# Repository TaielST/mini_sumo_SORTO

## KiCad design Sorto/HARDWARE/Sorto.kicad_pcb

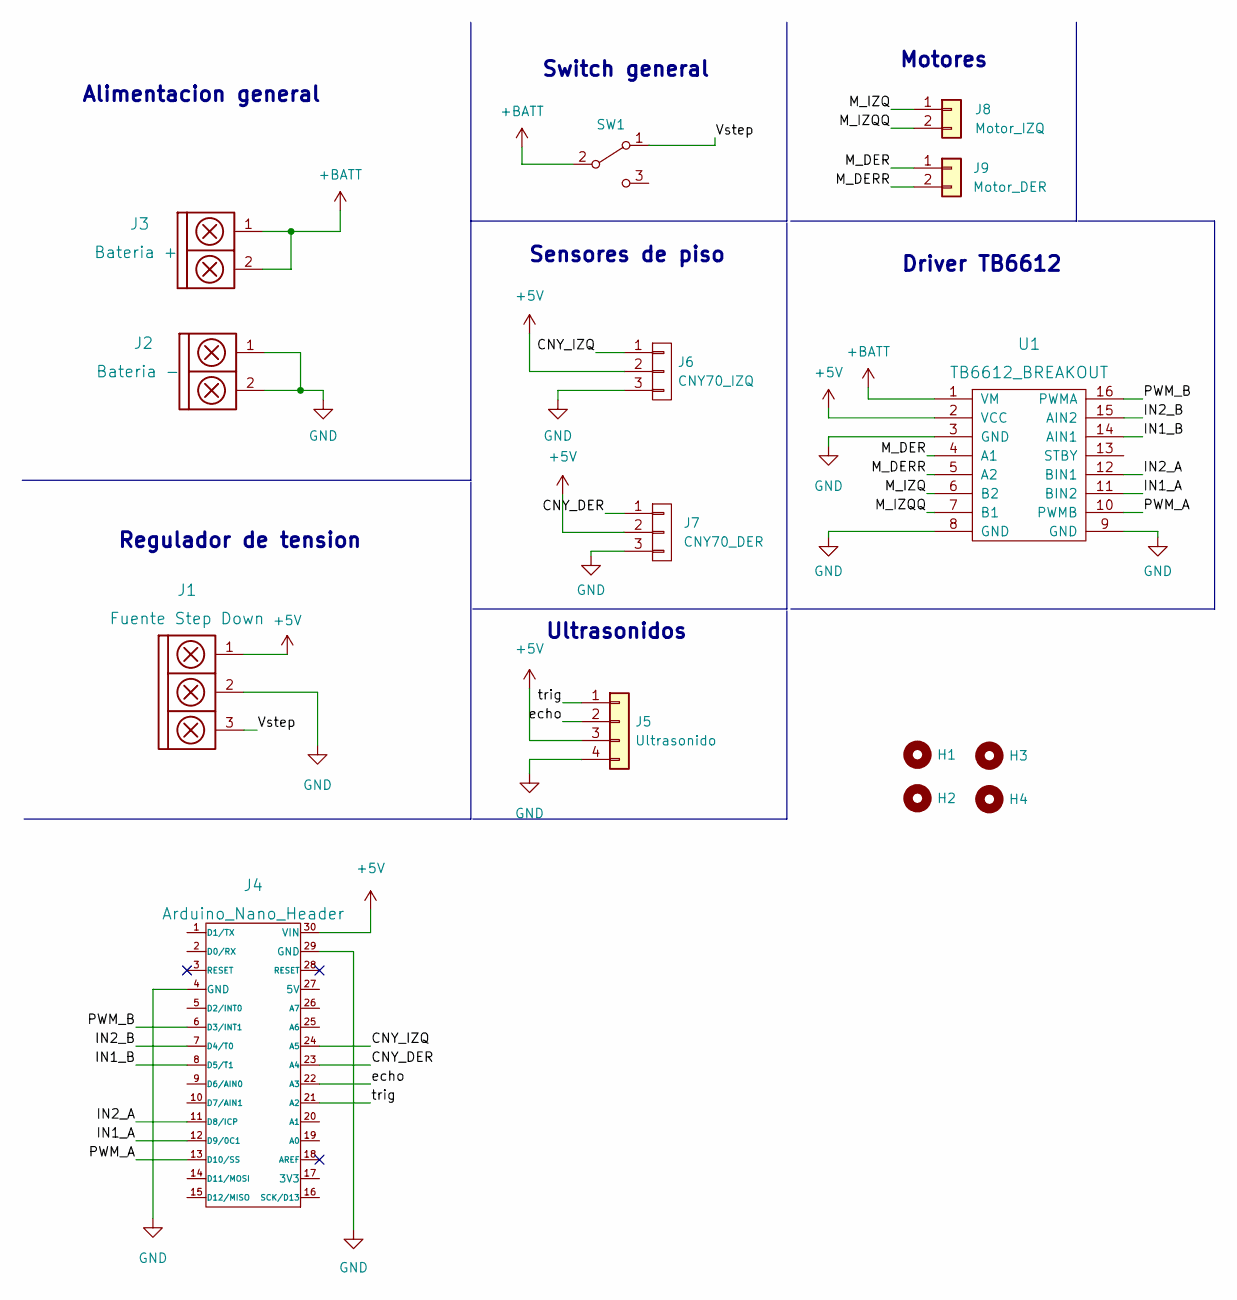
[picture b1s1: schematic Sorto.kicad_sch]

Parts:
H1, H2, H3, H4: Mounting_Hole; hole_3mm
J1: Fuente Step Down; BORNERA3_AZUL
J2: Bateria -; BORNERA2_AZUL
J3: Bateria +; BORNERA2_AZUL
J4: Arduino_Nano_Header; arduino_nano_header
J5: Ultrasonido; pin_strip_4
J6: CNY70_IZQ; Pin_Header_3
J7: CNY70_DER; Pin_Header_3
J8: Motor_IZQ; BORNERA2_AZUL
J9: Motor_DER; BORNERA2_AZUL
SW1: SW_SPDT; SW_SPDT_TH_Vertical
U1: TB6612_BREAKOUT; TB6612_Breakout

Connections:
+5V: J1.1, J4.30 (VIN), J5.3, J6.2, J7.2, U1.2 (VCC)
+BATT: J3.1, J3.2, SW1.2 (B), U1.1 (VM)
/CNY_DER: J4.23 (A4), J7.1
/CNY_IZQ: J4.24 (A5), J6.1
/IN1_A: J4.12 (D9/0C1), U1.11 (BIN2)
/IN1_B: J4.8 (D5/T1), U1.14 (AIN1)
/IN2_A: J4.11 (D8/ICP), U1.12 (BIN1)
/IN2_B: J4.7 (D4/T0), U1.15 (AIN2)
/M_DER: J9.1, U1.4 (A1)
/M_DERR: J9.2, U1.5 (A2)
/M_IZQ: J8.1, U1.6 (B2)
/M_IZQQ: J8.2, U1.7 (B1)
/PWM_A: J4.13 (D10/SS), U1.10 (PWMB)
/PWM_B: J4.6 (D3/INT1), U1.16 (PWMA)
/Vstep: J1.3, SW1.1 (A)
/echo: J4.22 (A3), J5.2
/trig: J4.21 (A2), J5.1
GND: J1.2, J2.1, J2.2, J4.4 (GND), J4.29 (GND), J5.4, J6.3, J7.3, U1.3 (GND), U1.8 (GND), U1.9 (GND)

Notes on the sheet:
Driver TB6612
Ultrasonidos
Switch general
Sensores de piso
Regulador de tension
Alimentacion general
Motores

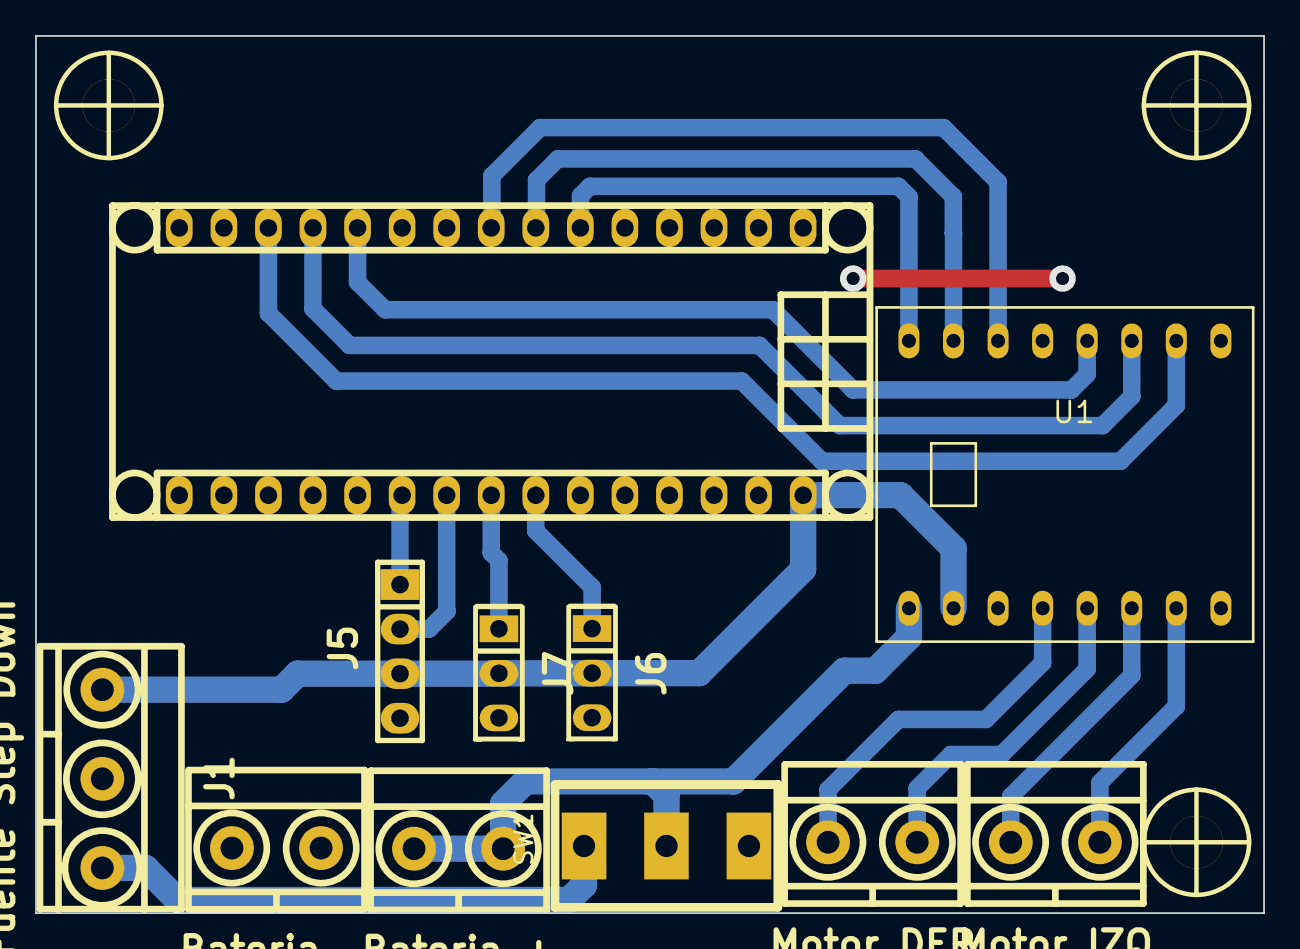
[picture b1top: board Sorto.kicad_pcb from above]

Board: 2 copper layers, 70.0 x 50.0 mm, 14 parts (0 on the bottom side), 18 nets.
